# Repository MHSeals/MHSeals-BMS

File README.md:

# MHSeals-BMS
Battery management board for 4S Li-Po
### Features
 - Cell monitoring
 - Cell balancing
 - Hot-swap

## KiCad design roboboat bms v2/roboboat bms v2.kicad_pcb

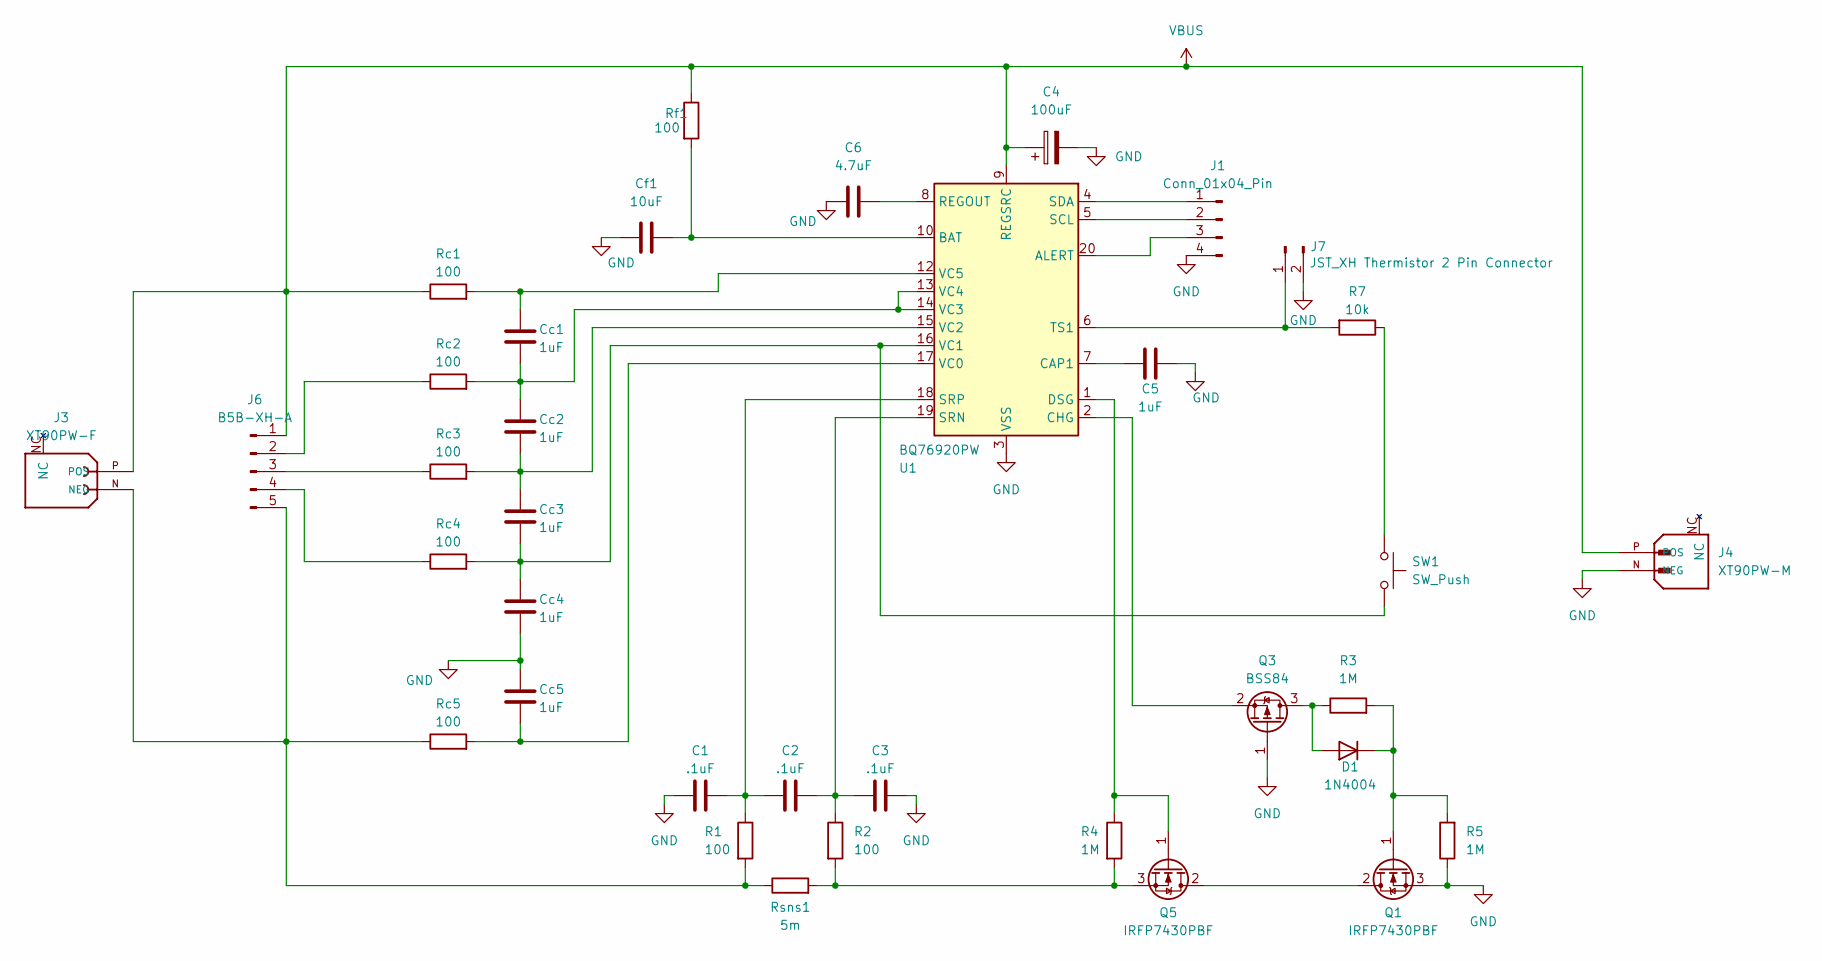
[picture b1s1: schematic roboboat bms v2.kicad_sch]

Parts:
C1, C2, C3: .1uF; C_0603_1608Metric; Mouser PN 810-C1608X7R1H104K
C4: 100uF; CP_Radial_D6.3mm_P2.50mm; Mouser PN 710-860010473007
C5: 1uF; C_0805_2012Metric; Mouser PN 187-CL21B105KAFNNNG
C6: 4.7uF; C_1206_3216Metric; Mouser PN 80-C1206C475K3PAC
Cc1, Cc2, Cc3, Cc4, Cc5: 1uF; C_0603_1608Metric; Mouser PN 187-CL10A105KA8NFNC
Cf1: 10uF; C_1206_3216Metric; Mouser PN 963-TMK316BJ106KL-T
D1: 1N4004; D_DO-41_SOD81_P10.16mm_Horizontal; Mouser PN 637-1N4004
J1: Conn_01x04_Pin; PinHeader_1x04_P2.54mm_Vertical
J3: XT90PW-F; AMASS_XT90PW-F; PARTREV V00
J4: XT90PW-M; AMASS_XT90PW-M; PARTREV V00
J6: B5B-XH-A; JST_XH_B5B-XH-A_1x05_P2.50mm_Vertical
J7: JST_XH Thermistor 2 Pin Connector; JST_XH_B2B-XH-A_1x02_P2.50mm_Vertical; Mouser PN 306-B2BXHALFSNP
Q1, Q5: IRFP7430PBF; TO-247-3_Vertical; Mouser PN 942-IRFP7430PBF
Q3: BSS84; SOT-23; Mouser PN 512-BSS84
R1, R2: 100; R_1206_3216Metric; Mouser PN 603-RE1206FRE07100RL
R3, R4, R5: 1M; R_0603_1608Metric; Mouser PN 71-CRCW0603-1.0M-E3
R7: 10k; R_0603_1608Metric; Mouser PN 755-ESR03EZPJ103
Rc1, Rc2, Rc3, Rc4, Rc5: 100; R_1206_3216Metric; Mouser PN 603-RE1206FRE07100RL
Rf1: 100; R_1206_3216Metric; Mouser PN 603-RE1206FRE07100RL
Rsns1: 5m; R_2512_6332Metric; Mouser PN 708-CSNL2512FTL500
SW1: SW_Push; SW_PUSH_6mm; Mouser PN 179-TS026660BK160LCR
U1: BQ76920PW; TSSOP-20_4.4x6.5mm_P0.65mm; Mouser PN 595-BQ7692003PW

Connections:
GND: C1.1, C3.2, C4.2, C5.2, C6.1, Cc4.2, Cc5.1, Cf1.1, J1.4, J4.N (NEG), J7.2, Q1.3 (S), Q3.1 (G), R5.1, U1.3 (VSS)
unnamed: D1.2 (A), Q3.3 (D), R3.1
unnamed: D1.1 (K), Q1.1 (G), R3.2, R5.2
unnamed: J1.1, U1.4 (SDA)
unnamed: J1.2, U1.5 (SCL)
unnamed: J1.3, U1.20 (ALERT)
unnamed: J3.N (NEG), J6.5, R1.2, Rc5.1, Rsns1.1
unnamed: J6.2, Rc2.1
unnamed: J6.3, Rc3.1
unnamed: J6.4, Rc4.1
unnamed: J7.1, R7.2, U1.6 (TS1)
unnamed: Q1.2 (D), Q5.2 (D)
unnamed: Q3.2 (S), U1.2 (CHG)
unnamed: Q5.1 (G), R4.1, U1.1 (DSG)
unnamed: Q5.3 (S), R2.2, R4.2, Rsns1.2
unnamed: R7.1, SW1.1
unnamed: Cf1.2, Rf1.2, U1.10 (BAT)
unnamed: C5.1, U1.7 (CAP1)
unnamed: C6.2, U1.8 (REGOUT)
unnamed: C2.2, C3.1, R2.1, U1.19 (SRN)
unnamed: C1.2, C2.1, R1.1, U1.18 (SRP)
unnamed: Cc5.2, Rc5.2, U1.17 (VC0)
unnamed: Cc3.2, Cc4.1, Rc4.2, SW1.2, U1.16 (VC1)
unnamed: Cc2.2, Cc3.1, Rc3.2, U1.15 (VC2)
unnamed: Cc1.2, Cc2.1, Rc2.2, U1.13 (VC4), U1.14 (VC3)
unnamed: Cc1.1, Rc1.2, U1.12 (VC5)
VBUS: C4.1, J3.P (POS), J4.P (POS), J6.1, Rc1.1, Rf1.1, U1.9 (REGSRC)

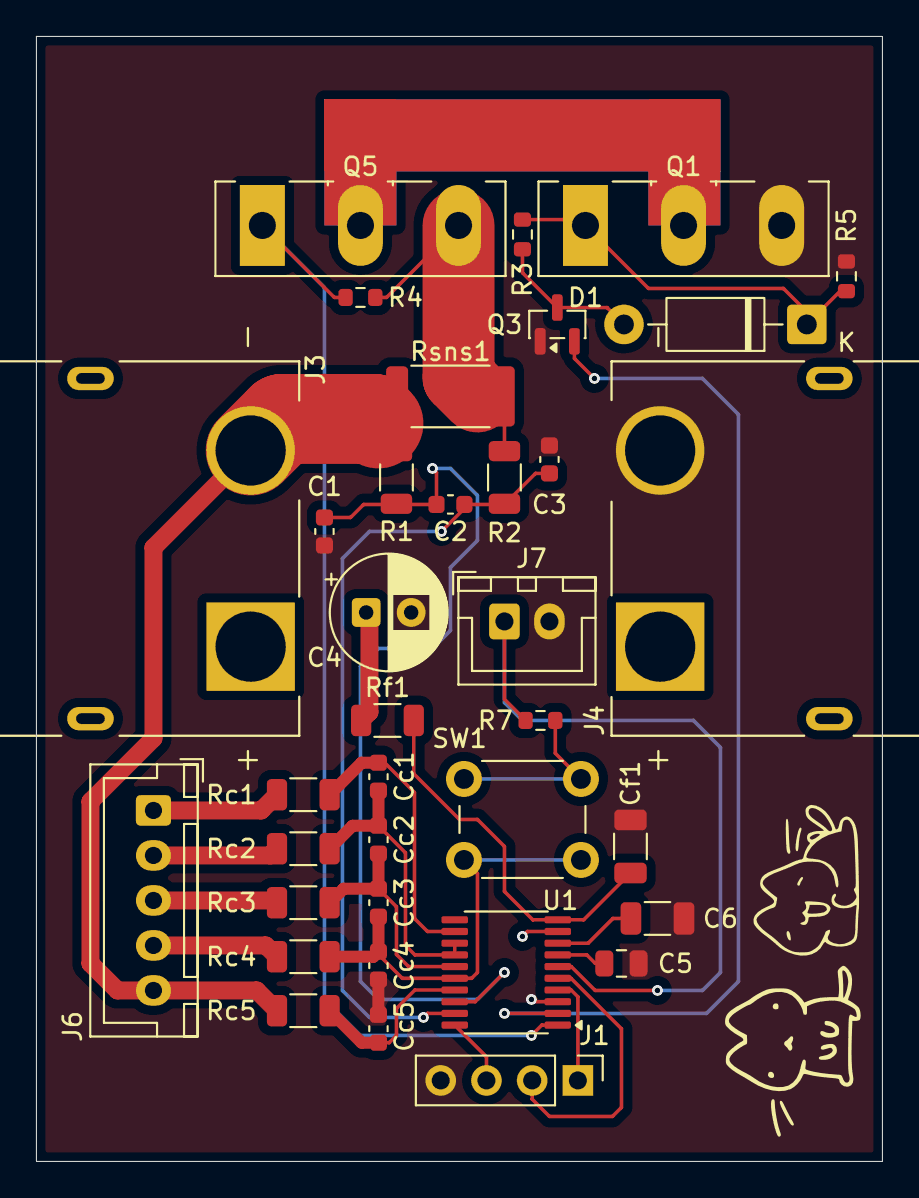
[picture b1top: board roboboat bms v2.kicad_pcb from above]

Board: 4 copper layers, 47.0 x 62.5 mm, 36 parts (0 on the bottom side), 27 nets.

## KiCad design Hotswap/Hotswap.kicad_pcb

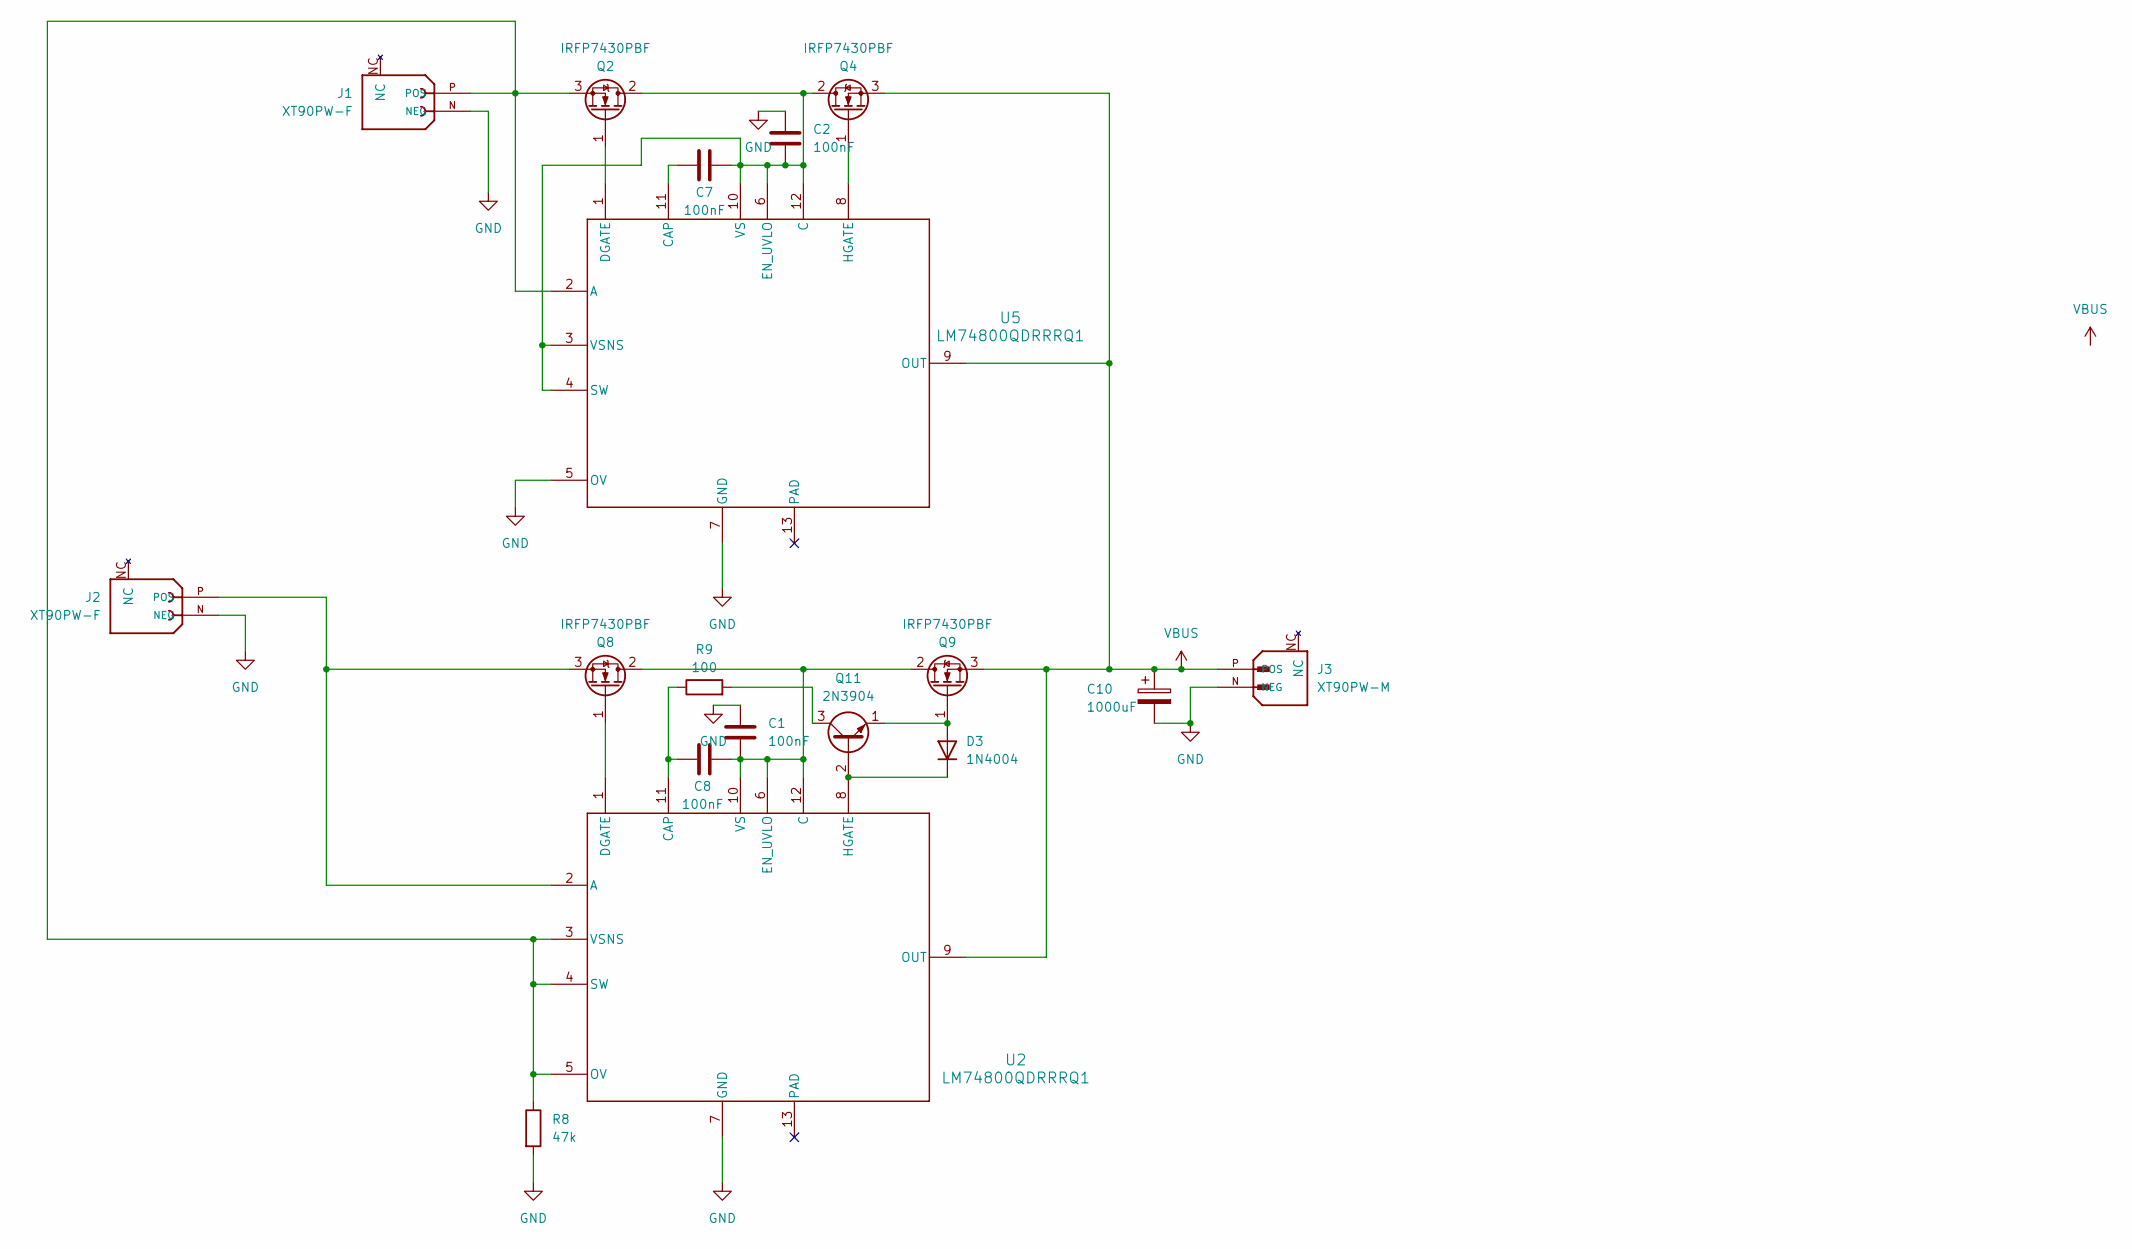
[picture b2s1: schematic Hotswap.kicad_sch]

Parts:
C1, C2: 100nF; C_0603_1608Metric
C7, C8: 100nF; C_0603_1608Metric; Mouser PN 791-1210B104K250CT
C10: 1000uF; CP_Radial_D12.5mm_P5.00mm; Mouser PN 581-REF1216102M025K
D3: 1N4004; D_DO-41_SOD81_P10.16mm_Horizontal; Mouser PN 637-1N4004
J1, J2: XT90PW-F; AMASS_XT90PW-F; PARTREV V00
J3: XT90PW-M; AMASS_XT90PW-M; PARTREV V00
Q2, Q4, Q8, Q9: IRFP7430PBF; TO-247-3_Vertical; Mouser PN 942-IRFP7430PBF
Q11: 2N3904; TO-92_Inline; Mouser PN 637-2N3904
R8: 47k; R_0603_1608Metric; Mouser PN 71-CRCW060347K0FKEC
R9: 100; R_1206_3216Metric; Mouser PN 603-RE1206FRE07100RL
U2, U5: LM74800QDRRRQ1; WSON-12-1EP_3x3mm_P0.5mm_EP1.5x2.5mm; Mouser PN 595-LM74800QDRRRQ1

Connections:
GND: C1.1, C2.1, C10.2, J1.N (NEG), J2.N (NEG), J3.N (NEG), R8.2, U2.7 (GND), U5.5 (OV), U5.7 (GND)
unnamed: D3.2 (A), Q9.1 (G), Q11.1 (E)
unnamed: D3.1 (K), Q11.2 (B), U2.8 (HGATE)
unnamed: J1.P (POS), Q2.3 (S), R8.1, U2.3 (VSNS), U2.4 (SW), U2.5 (OV), U5.2 (A)
unnamed: J2.P (POS), Q8.3 (S), U2.2 (A)
unnamed: C2.2, C7.2, Q2.2 (D), Q4.2 (D), U5.3 (VSNS), U5.4 (SW), U5.6 (EN_UVLO), U5.10 (VS), U5.12 (C)
unnamed: Q2.1 (G), U5.1 (DGATE)
unnamed: Q4.1 (G), U5.8 (HGATE)
unnamed: C1.2, C8.2, Q8.2 (D), Q9.2 (D), U2.6 (EN_UVLO), U2.10 (VS), U2.12 (C)
unnamed: Q8.1 (G), U2.1 (DGATE)
unnamed: Q11.3 (C), R9.2
unnamed: C8.1, R9.1, U2.11 (CAP)
unnamed: C7.1, U5.11 (CAP)
VBUS: C10.1, J3.P (POS), Q4.3 (S), Q9.3 (S), U2.9 (OUT), U5.9 (OUT)

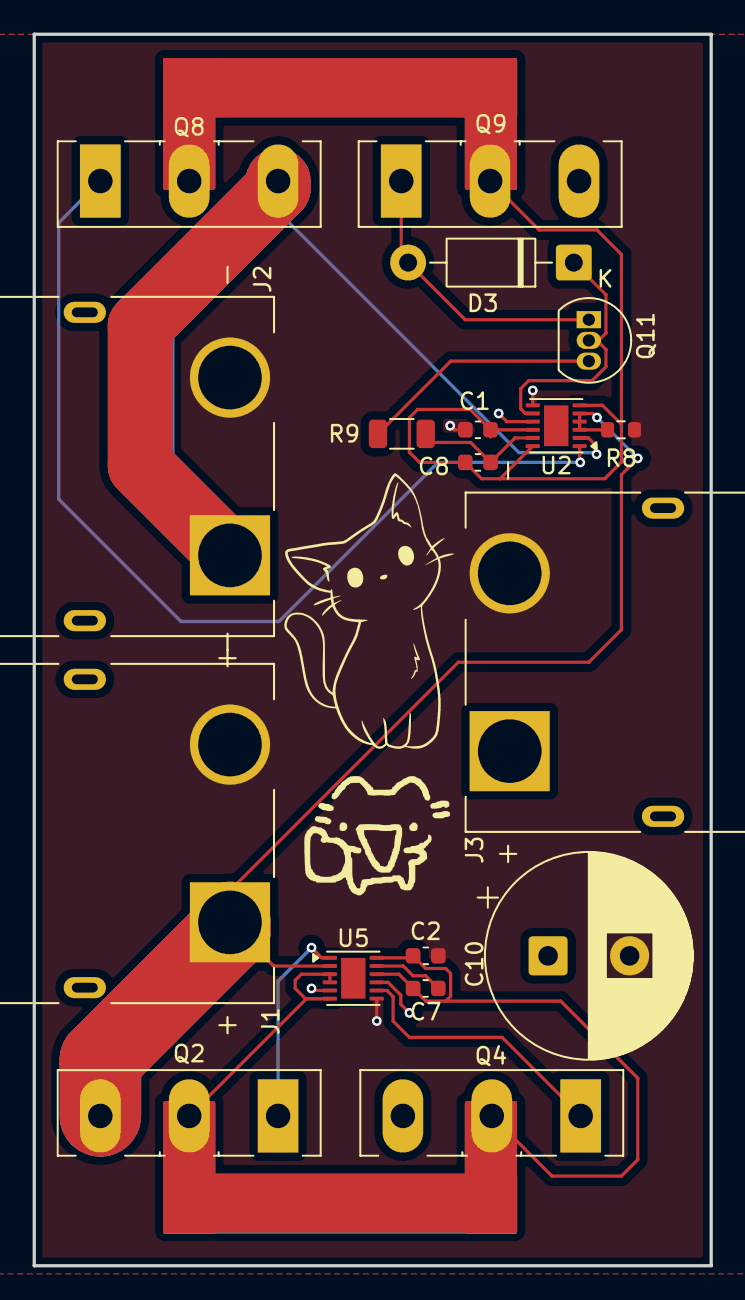
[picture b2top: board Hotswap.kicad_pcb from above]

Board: 4 copper layers, 41.5 x 75.5 mm, 18 parts (0 on the bottom side), 14 nets.

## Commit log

2025-05-29 add chips symbols/footprints
2025-05-29 Changed placement of pins in symbol editor
2025-05-29 Updated schematic and symbols
    Changed placement of EN/UVLO because reading datasheet of where it connects didn't match the schematic.
2025-11-04 updating schematic with new version with BMS
2025-12-07 Update to new version of schematic Separate hotswap and BMS
2025-12-19 update MOSFET to IRF7430
2025-12-19 Update to improve current handling
